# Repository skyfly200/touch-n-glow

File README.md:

# touch-n-glow

Touch pad and modular addressable LED system breakout

![alt text][pcb-bottom]

![alt text][pcb-top]

![alt text][pcb-assembled]

[pcb-bottom]: https://github.com/skyfly200/touch-n-glow/blob/master/IMG_20191026_140133_855.jpg?raw=true "PCB Bottom"
[pcb-top]: https://github.com/skyfly200/touch-n-glow/blob/master/IMG_20191026_140133_859.jpg?raw=true "PCB Top"
[pcb-assembled]: https://github.com/skyfly200/touch-n-glow/blob/master/IMG_20191026_140133_872.jpg?raw=true "PCB Assembled"

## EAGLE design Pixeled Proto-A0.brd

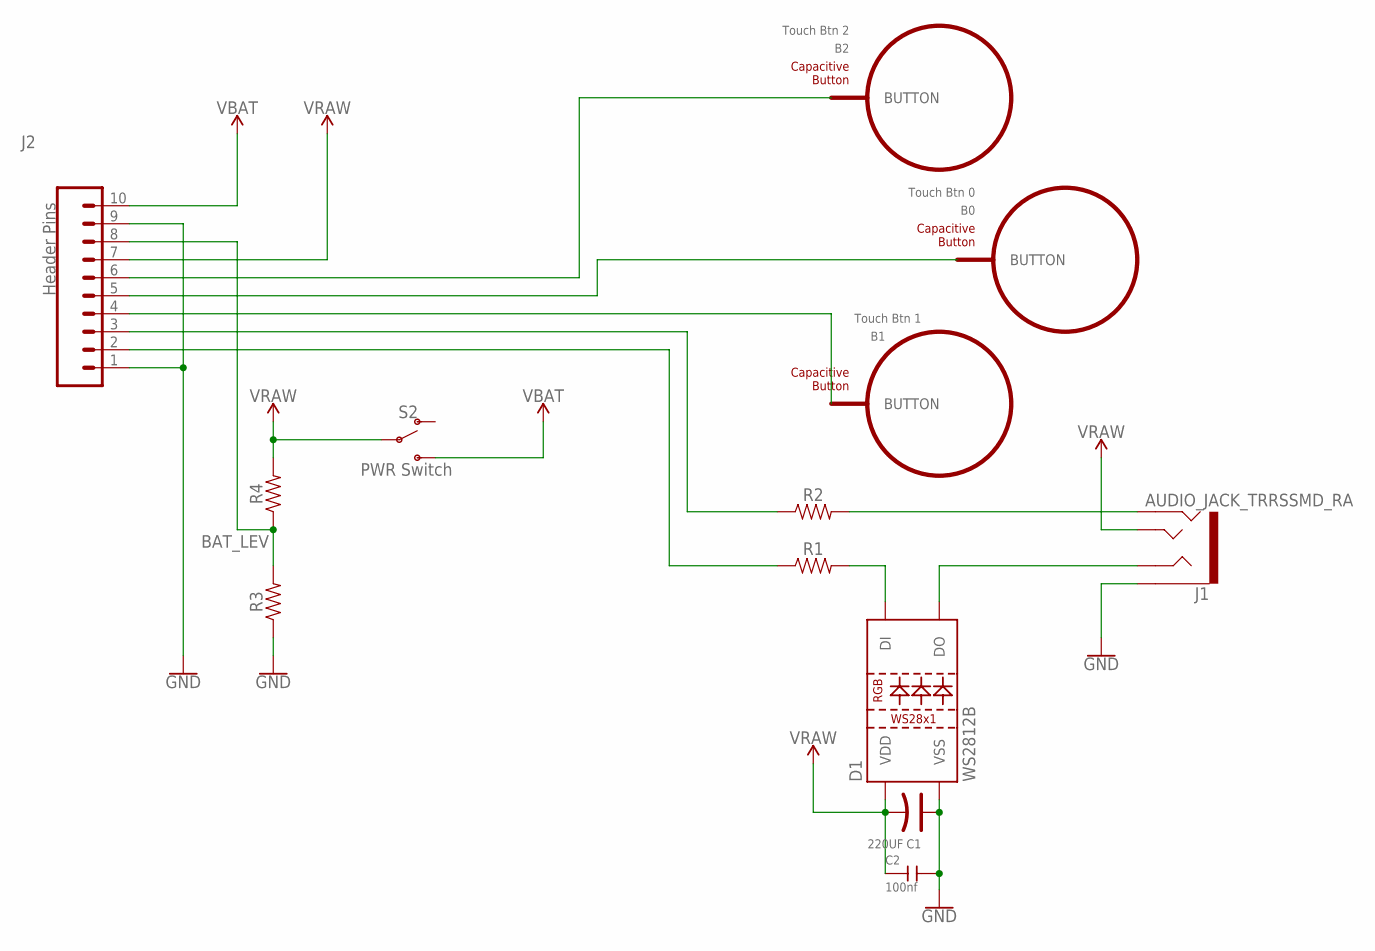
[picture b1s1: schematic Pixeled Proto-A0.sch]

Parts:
B0: Touch Btn 0; BUTTON_PASSIVE_8MM
B1: Touch Btn 1; BUTTON_PASSIVE_12MM
B2: Touch Btn 2; BUTTON_PASSIVE_12MM
C1: 220UF; ELECTRO-SMD-C-6MM
C2: 100nf; C0805
D1: WS2812B
J1: AUDIO_JACK_TRRSSMD_RA; AUDIO_JACK_3.5MM_TRRS_SMD_RA
J2: Header Pins; 1X10
R1, R2, R3, R4: 0805
S2: PWR Switch; SWITCH_SPST_SMD_A

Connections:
BAT_LEV: J2.8, R3.2, R4.1
GND: C1.+, C2.2, D1.3 (VSS), J1.EARTH, J2.1, J2.9, R3.1
unnamed: D1.4 (DI), R1.2
unnamed: D1.2 (DO), J1.RING1
unnamed: J2.3, R2.1
unnamed: J2.2, R1.1
unnamed: J1.RING2, R2.2
T0: B2.BUTTON, J2.6
T1: B0.BUTTON, J2.5
T2: B1.BUTTON, J2.4
VRAW: C1.-, C2.1, D1.1 (VDD), J1.TIP, J2.7, R4.2, S2.2
V_BATT: J2.10, S2.3 (S)

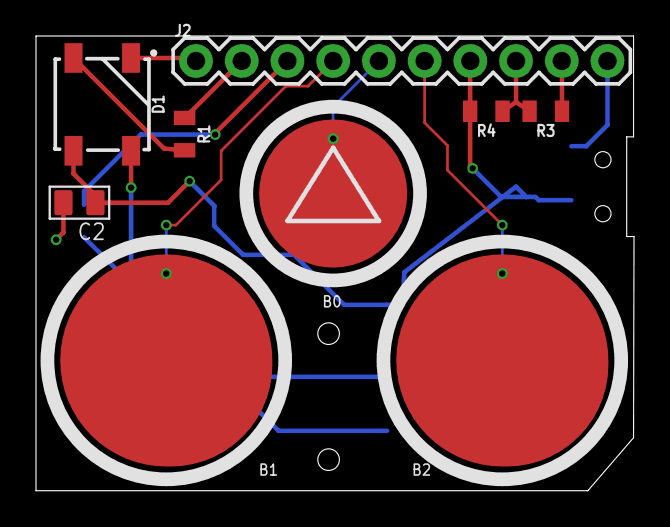
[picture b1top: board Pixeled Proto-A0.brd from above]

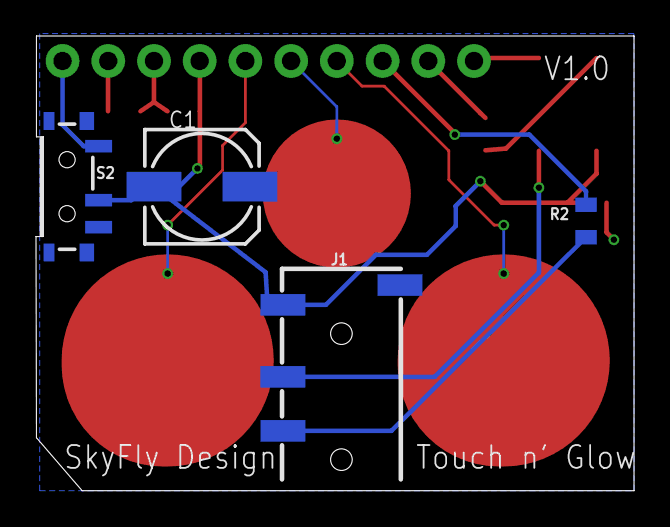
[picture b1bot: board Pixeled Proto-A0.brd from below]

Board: 2 copper layers, 33.2 x 25.3 mm, 13 parts (4 on the bottom side), 12 nets.

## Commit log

2019-12-20 upload eagle files

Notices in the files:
parts and their libraries:
PatternAgents-TouchWidgets: License : http://creativecommons.org/licenses/by-sa/4.0/ (Creative Commons 4.0)
PatternAgents-TouchWidgets: License : http://creativecommons.org/licenses/by-sa/3.1/ (Creative Commons 3.1)
